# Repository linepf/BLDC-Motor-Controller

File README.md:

# BLDC-Motor-Controller

### “STM32 기반 BLDC 모터 제어기"는 STM32F767 MCU와 직접 설계·제작한 인버터 회로(PCB)를 기반으로 한 BLDC 모터 제어기입니다.
### 6스텝 구동 방식을 적용하여 홀센서 및 BEMF(센서리스) 신호 기반의 구동을 수행합니다.

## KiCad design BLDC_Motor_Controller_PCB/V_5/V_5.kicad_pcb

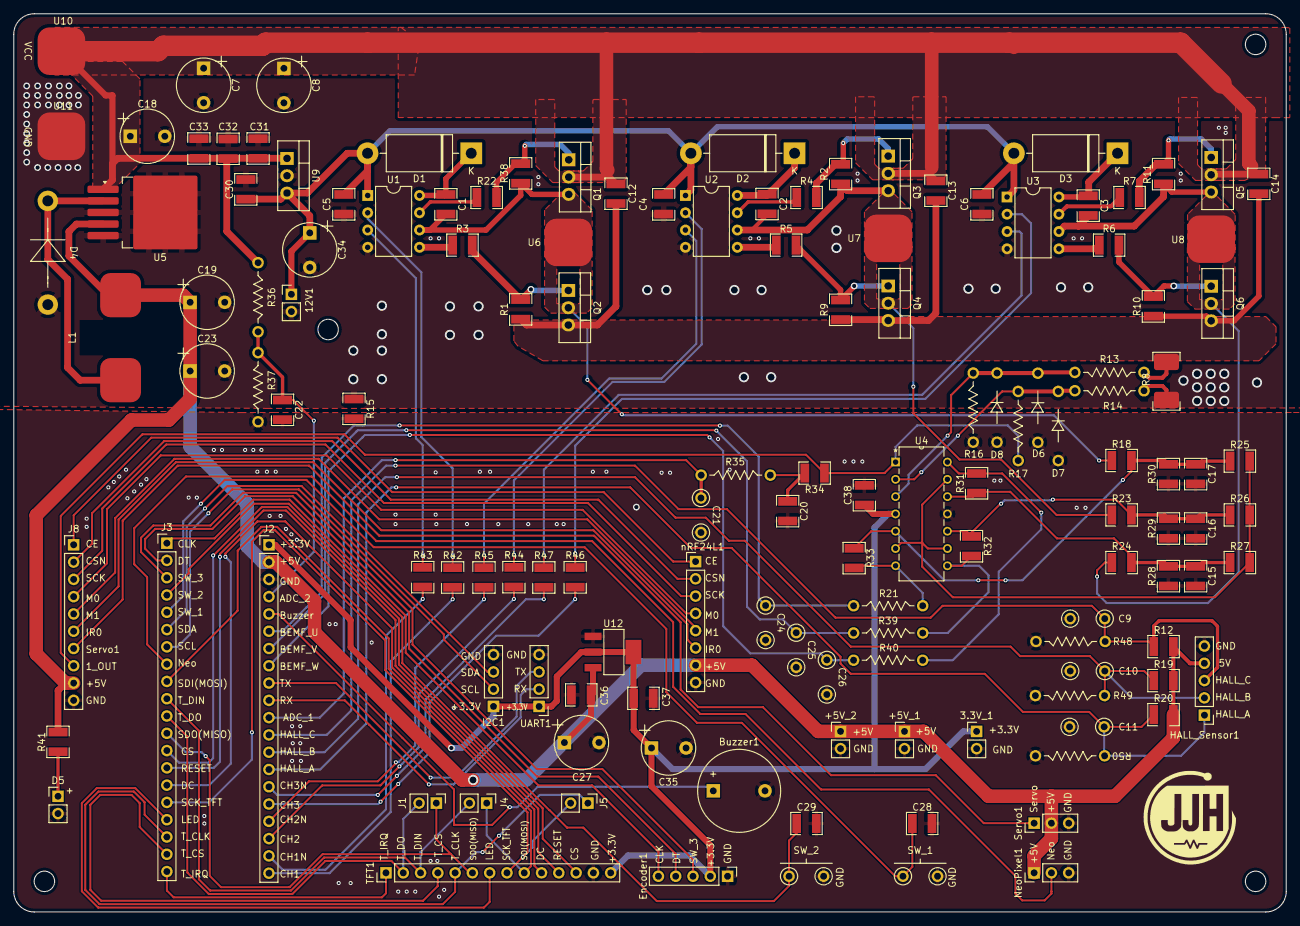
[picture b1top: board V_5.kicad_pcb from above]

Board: 2 copper layers, 187.0 x 132.0 mm, 136 parts (0 on the bottom side), 88 nets.

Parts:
3.3V_1: +3.3V; Pin_2_P2.54mm_Vertical
12V1: +12V; Pin_2_P2.54mm_Vertical
+5V_1, +5V_2: +5V; Pin_2_P2.54mm_Vertical
Buzzer1: Buzzer; Buzzer_P7.6mm
C1, C2, C3, C12, C13, C14: 2.2uf; R1210
C4, C5, C6, C15, C16, C17, C20, C22, C28, C29, C30, C31, C32, C33, C36, C37, C38: 0.1uf; R1210
C7, C19: 220uf; CAP_P5.08mm
C8, C18: 680uf; CAP_P5.08mm
C9, C10, C11: 0.01uf; CAP_103
C21: -999; CAP_103
C23: -999; CAP_P5.08mm
C24, C25, C26: 0.1uf; CAP_103
C27, C35: 10uf; CAP_P5.08mm
C34: 100uf; CAP_P5.08mm
D1, D2, D3: 1N5822; D_DO-201AD_P15.24mm_Horizontal
D4: 1N5824; Big_Diode
D5: LED
D6, D7: 1N4728A_3.3V; Dip_Diode
D8: D; Dip_Diode
Encoder1: Encoder; Pin_5_P2.54mm_Vertical
HALL_Sensor1: Hall sensor; Pin_5_P2.54mm_Vertical
I2C1: I2C; Pin_4_P2.54mm_Vertical
J1, J4, J5: Conn_01x02; Pin_2_P2.54mm_Vertical
J2, J3: Conn_01x20; Pin_20_P2.54mm_Vertical
J8: Conn_01x10; Pin_10_P2.54mm_Vertical
L1: 33uH; POWER_Inductor
NeoPixel1: NeoPixel; Pin_3_P2.54mm_Vertical
Q1, Q2, Q3, Q4, Q5, Q6: IRF3205; TO-220-3_Vertical
R1, R2, R9, R10, R11, R12, R18, R19, R20, R23, R24, R25, R26, R27, R34, R38, R41: 10k; R1210
R3, R4, R5, R6, R7, R22, R42, R43, R44, R45, R46, R47: 100; R1210
R8: 0.02; R0.02
R13, R14, R16, R17, R21, R35, R39, R40: -999; Dip_Resistor
R15: 0; R1210
R28, R29, R30: 1.6k; R1210
R31, R32, R33: 1M; R1210
R36: 47k; Dip_Resistor
R37: 10k; Dip_Resistor
R48, R49, R50: 20k; Dip_Resistor
SW_1: SW_1; SW_PIN2
SW_2: SW_2; SW_PIN2
Servo1: Servo; Pin_3_P2.54mm_Vertical
TFT1: Pin_14_P2.54mm_Vertical
U1, U2, U3: IR2101; DIP_8_IC
U4: TLV2374IPWR; TLV2374IN_Dip
U5: LM2596S-5; TO-263-5_TabPin3
U6, U7, U8, U10, U11: BLDC_PAD
U9: LM7812_TO220; TO-220-3_Vertical
U12: SOT-223-3_pin4
UART1: UART; Pin_4_P2.54mm_Vertical
nRF24L1: nRF24L01; Pin_8_P2.54mm_Vertical

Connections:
1IN+: D6.1 (K), D8.1 (K), R13.2, R16.2, U4.3 (1IN+)
1IN-: D7.1 (K), R14.2, R17.1, U4.2 (1IN-)
1OUT: J8.8, R17.2, R34.1, U4.1 (1OUT)
2IN+: C17.1, R18.2, R25.1, R30.2, R33.1, U4.5 (2IN+)
2OUT: C24.1, J2.6, R21.1
3.3v: 3.3V_1.1, C35.1, C37.1, C38.1, Encoder1.2, I2C1.1, J2.1, TFT1.14 (VCC), U4.4 (VDD), U12.2 (VOUT), U12.4 (VOUT), UART1.1
3IN+: C16.1, R23.2, R26.1, R29.2, R32.1, U4.10 (3IN+)
3OUT: C25.1, J2.7, R39.1
4IN+: C15.1, R24.2, R27.1, R28.2, R31.1, U4.12 (4IN+)
4OUT: C26.1, J2.8, R40.1
5V: +5V_1.1, +5V_2.1, C19.1, C23.1, C27.1, C36.1, HALL_Sensor1.4 (5V), J2.2, J8.9, L1.2, NeoPixel1.1, R12.2, R19.2, R20.2, R41.2, Servo1.2, U5.4 (FB), U12.3 (VIN), nRF24L1.7
12V: 12V1.1, C4.1, C5.1, C6.1, C30.1, C34.1, D1.2 (A), D2.2 (A), D3.2 (A), U1.1 (VCC), U2.1 (VCC), U3.1 (VCC), U9.3 (VO)
ADC_1: C21.1, J2.11, R35.1
ADC_2: C22.1, J2.4, R36.2, R37.2
Buzzer: Buzzer1.1 (+), J2.5
CE: J8.1, nRF24L1.1
CLK: Encoder1.5, J3.1
CS: J3.13, TFT1.12 (CS)
CSN: J8.2, nRF24L1.2
DC: J3.15, TFT1.10 (DC)
DT: Encoder1.4, J3.2
GND: 3.3V_1.2, +5V_1.2, +5V_2.2, Buzzer1.2 (-), C9.2, C10.2, C11.2, C15.2, C16.2, C17.2, C20.2, C21.2, C22.2, C24.2, C25.2, C26.2, C27.2, C28.2, C29.2, C35.2, C36.2, C37.2, C38.2, D5.2 (A), D6.2 (A), D7.2 (A), D8.2 (A), Encoder1.1, HALL_Sensor1.5 (Gnd), I2C1.4, J2.3, J8.10, NeoPixel1.3, R15.2, R16.1, R28.1, R29.1, R30.1, R37.1, R48.2, R49.2, R50.2, SW_1.2, SW_2.2, Servo1.3, TFT1.13 (GND), U4.11 (GND), U12.1 (GND), UART1.4, nRF24L1.8
GNDPWR: 12V1.2, C4.2, C5.2, C6.2, C7.2, C8.2, C18.2, C19.2, C23.2, C30.2, C31.2, C32.2, C33.2, C34.2, D4.2 (A), R8.1, R14.1, R15.1, U1.4 (COM), U2.4 (COM), U3.4 (COM), U5.3 (GND), U5.5 (~ON/OFF), U9.2 (GND), U11.1 (PAD)
Hall_A: C11.1, HALL_Sensor1.1 (Hall_A), J2.14, R20.1, R50.1
Hall_B: C10.1, HALL_Sensor1.2 (Hall_B), J2.13, R19.1, R49.1
Hall_C: C9.1, HALL_Sensor1.3 (Hall_C), J2.12, R12.1, R48.1
I2C_SCL: I2C1.2, J3.7
I2C_SDA: I2C1.3, J3.6
IRQ: J8.6, nRF24L1.6
LED: J3.17, TFT1.7 (LED)
MI: J8.5, nRF24L1.5
MO: J8.4, nRF24L1.4
NeoPixel: J3.8, NeoPixel1.2
unnamed: C20.1, R34.2, R35.2
unnamed: C1.1, D1.1 (K), U1.8 (VB)
unnamed: C2.1, D2.1 (K), U2.8 (VB)
unnamed: C3.1, D3.1 (K), U3.8 (VB)
unnamed: D4.1 (K), L1.1, U5.2 (OUT)
unnamed: D5.1 (K), R41.1
unnamed: C12.2, C13.2, C14.2, Q2.3 (S), Q4.3 (S), Q6.3 (S), R1.1, R8.2, R9.1, R10.1, R13.1
unnamed: R42.2, U1.2 (HIN)
unnamed: R22.1, U1.7 (HO)
unnamed: R43.2, U1.3 (LIN)
unnamed: R3.1, U1.5 (LO)
unnamed: R44.2, U2.2 (HIN)
unnamed: R4.1, U2.7 (HO)
unnamed: R45.2, U2.3 (LIN)
unnamed: R5.1, U2.5 (LO)
unnamed: R46.2, U3.2 (HIN)
unnamed: R7.1, U3.7 (HO)
unnamed: R47.2, U3.3 (LIN)
unnamed: R6.1, U3.5 (LO)
unnamed: R21.2, R33.2, U4.7 (2OUT)
unnamed: R32.2, R39.2, U4.8 (3OUT)
unnamed: R31.2, R40.2, U4.14 (4OUT)
Phase_U: C1.2, Q1.3 (S), Q2.2 (D), R18.1, R38.1, U1.6 (VS), U6.1 (PAD)
Phase_V: C2.2, Q3.3 (S), Q4.2 (D), R2.1, R23.1, U2.6 (VS), U7.1 (PAD)
Phase_W: C3.2, Q5.3 (S), Q6.2 (D), R11.1, R24.1, U3.6 (VS), U8.1 (PAD)
RESET: J3.14, TFT1.11 (RESET)
SCK: J8.3, nRF24L1.3
SCK_TFT: J3.16, J5.2, TFT1.8 (SCK)
SDI(MOSI): J3.9, J4.1, TFT1.9 (SDI(MOSI))
SDO(MISO): J1.1, J3.12, TFT1.6 (SDO(MISO))
SW_1: C28.1, J3.5, SW_1.1
SW_2: C29.1, J3.4, SW_2.1
SW_3: Encoder1.3, J3.3
Servo: J8.7, Servo1.1
TIM1_CH1: J2.20, R42.1
TIM1_CH1N: J2.19, R43.1
TIM1_CH2: J2.18, R44.1
TIM1_CH2N: J2.17, R45.1
TIM1_CH3: J2.16, R46.1
TIM1_CH3N: J2.15, R47.1
T_CLK: J3.18, J5.1, TFT1.5 (T_CLK)
T_CS: J3.19, TFT1.4 (T_CS)
T_DIN: J3.10, J4.2, TFT1.3 (T_DIN)
T_DO: J1.2, J3.11, TFT1.2 (T_DO)
T_IRQ: J3.20, TFT1.1 (T_IRQ)
UART_RX: J2.10, UART1.2
UART_TX: J2.9, UART1.3
U_Bot: Q2.1 (G), R1.2, R3.2
U_Top: Q1.1 (G), R22.2, R38.2
VCC: C7.1, C8.1, C12.1, C13.1, C14.1, C18.1, C31.1, C32.1, C33.1, Q1.2 (D), Q3.2 (D), Q5.2 (D), R36.1, U5.1 (VIN), U9.1 (VI), U10.1 (PAD)
V_Bot: Q4.1 (G), R5.2, R9.2
V_GND: R25.2, R26.2, R27.2, U4.6 (2IN-), U4.9 (3IN-), U4.13 (4IN-)
V_Top: Q3.1 (G), R2.2, R4.2
W_Bot: Q6.1 (G), R6.2, R10.2
W_Top: Q5.1 (G), R7.2, R11.2

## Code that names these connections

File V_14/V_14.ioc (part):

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Mcu.Name=STM32F767ZITx
Mcu.Package=LQFP144
Mcu.UserName=STM32F767ZITx
PA3.Signal=ADCx_IN3
PA5.Mode=Full_Duplex_Master
PA5.Signal=SPI1_SCK
PA6.Mode=Full_Duplex_Master
PA6.Signal=SPI1_MISO
PA7.Mode=Full_Duplex_Master
PA7.Signal=SPI1_MOSI
PB0.Mode=PWM Generation2 CH2 CH2N
PB0.Signal=TIM1_CH2N
PB1.GPIOParameters=GPIO_PuPd
PB1.GPIO_PuPd=GPIO_NOPULL
PB1.Mode=PWM Generation3 CH3 CH3N
PB1.Signal=TIM1_CH3N
PB10.GPIOParameters=GPIO_PuPd,GPIO_Label,GPIO_ModeDefaultEXTI
PB10.GPIO_Label=DT
PB10.GPIO_ModeDefaultEXTI=GPIO_MODE_IT_RISING_FALLING
PB10.GPIO_PuPd=GPIO_PULLUP
PB10.Signal=GPXTI10
PB11.GPIOParameters=GPIO_PuPd,GPIO_Label
PB11.GPIO_Label=CLK
PB11.GPIO_PuPd=GPIO_PULLUP
PB11.Signal=GPIO_Input
PB13.GPIOParameters=GPIO_PuPd
PB13.GPIO_PuPd=GPIO_NOPULL
PB13.Mode=PWM Generation1 CH1 CH1N
PB13.Signal=TIM1_CH1N
PB15.Mode=Asynchronous
PB15.Signal=USART1_RX
PB6.Mode=Asynchronous
PB6.Signal=USART1_TX
PC3.GPIOParameters=GPIO_Label,GPIO_ModeDefaultEXTI
PC3.GPIO_Label=HALL_A
PC3.GPIO_ModeDefaultEXTI=GPIO_MODE_IT_RISING_FALLING
PC3.Signal=GPXTI3
PD0.GPIOParameters=GPIO_Label,GPIO_ModeDefaultEXTI
PD0.GPIO_Label=HALL_B
PD0.GPIO_ModeDefaultEXTI=GPIO_MODE_IT_RISING_FALLING
PD0.Signal=GPXTI0
PD1.GPIOParameters=GPIO_Label,GPIO_ModeDefaultEXTI
PD1.GPIO_Label=CALL_C
PD1.GPIO_ModeDefaultEXTI=GPIO_MODE_IT_RISING_FALLING
PD1.Signal=GPXTI1
PD14.GPIOParameters=GPIO_Label,GPIO_ModeDefaultEXTI
PD14.GPIO_Label=BEMF_W
PD14.GPIO_ModeDefaultEXTI=GPIO_MODE_IT_RISING_FALLING
PD14.Signal=GPXTI14
PD15.GPIOParameters=GPIO_Label,GPIO_ModeDefaultEXTI
PD15.GPIO_Label=BEMF_U
PD15.GPIO_ModeDefaultEXTI=GPIO_MODE_IT_RISING_FALLING
PD15.Signal=GPXTI15
PE0.GPIOParameters=GPIO_PuPd,GPIO_Label
PE0.GPIO_Label=LCD_CLEAR
PE0.GPIO_PuPd=GPIO_PULLUP
PE0.Signal=GPIO_Input
PE10.GPIOParameters=PinState,GPIO_PuPd,GPIO_Label
PE10.GPIO_Label=Buzzer
PE10.GPIO_PuPd=GPIO_PULLDOWN
PE10.PinState=GPIO_PIN_RESET
PE10.Signal=GPIO_Output
PE11.Signal=S_TIM1_CH2
PE13.GPIOParameters=GPIO_PuPd
PE13.GPIO_PuPd=GPIO_NOPULL
PE13.Signal=S_TIM1_CH3
PE15.GPIOParameters=GPIO_PuPd,GPIO_Label
PE15.GPIO_Label=SW_3
PE15.GPIO_PuPd=GPIO_PULLUP
PE15.Signal=GPIO_Input
PE4.GPIOParameters=GPIO_PuPd,GPIO_Label,GPIO_ModeDefaultEXTI
PE4.GPIO_Label=SW_2
PE4.GPIO_ModeDefaultEXTI=GPIO_MODE_IT_FALLING
PE4.GPIO_PuPd=GPIO_PULLUP
PE4.Signal=GPXTI4
PE5.GPIOParameters=GPIO_Label
PE5.GPIO_Label=DC
PE5.Signal=GPIO_Output
PE6.GPIOParameters=GPIO_Label
PE6.GPIO_Label=RESET
PE6.Signal=GPIO_Output
PE8.Signal=GPIO_Analog
PE9.Signal=S_TIM1_CH1
PF12.GPIOParameters=GPIO_Label,GPIO_ModeDefaultEXTI
PF12.GPIO_Label=BEMF_V
PF12.GPIO_ModeDefaultEXTI=GPIO_MODE_IT_RISING_FALLING
PF12.Signal=GPXTI12
PF3.Signal=ADC3_IN9
PF8.GPIOParameters=GPIO_Label
PF8.GPIO_Label=CS
PF8.Signal=GPIO_Output
PF9.GPIOParameters=GPIO_Label
PF9.GPIO_Label=LED
PF9.Signal=GPIO_Output
PG0.GPIOParameters=GPIO_PuPd,GPIO_Label
PG0.GPIO_Label=SW_1
PG0.GPIO_PuPd=GPIO_PULLUP
PG0.Signal=GPIO_Input
RCC.HSE_VALUE=25000000
RCC.SYSCLKFreq_VALUE=112000000
RCC.SYSCLKSource=RCC_SYSCLKSOURCE_PLLCLK
board=custom

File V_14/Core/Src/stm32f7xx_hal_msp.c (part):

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    __HAL_RCC_GPIOB_CLK_ENABLE();
    __HAL_RCC_GPIOE_CLK_ENABLE();
    /**TIM1 GPIO Configuration
    PB0     ------> TIM1_CH2N
    PB1     ------> TIM1_CH3N
    PE9     ------> TIM1_CH1
    PE11     ------> TIM1_CH2
    PE13     ------> TIM1_CH3
    PB13     ------> TIM1_CH1N
    */
    GPIO_InitStruct.Pin = GPIO_PIN_0|GPIO_PIN_1|GPIO_PIN_13;
    GPIO_InitStruct.Mode = GPIO_MODE_AF_PP;
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

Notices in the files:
V_14/Core/Src/stm32f7xx_hal_msp.c:
Copyright (c) 2026 STMicroelectronics.
All rights reserved.
This software is licensed under terms that can be found in the LICENSE file
